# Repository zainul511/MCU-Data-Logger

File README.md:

This work was supported by material from:
Dalmaris, P. KiCad Like a Pro, 3rd Edition. Tech Explorations, 2021. ISBN 978-1-68489-093-4. 
KiCadLikeaPro3e_Course_Companion

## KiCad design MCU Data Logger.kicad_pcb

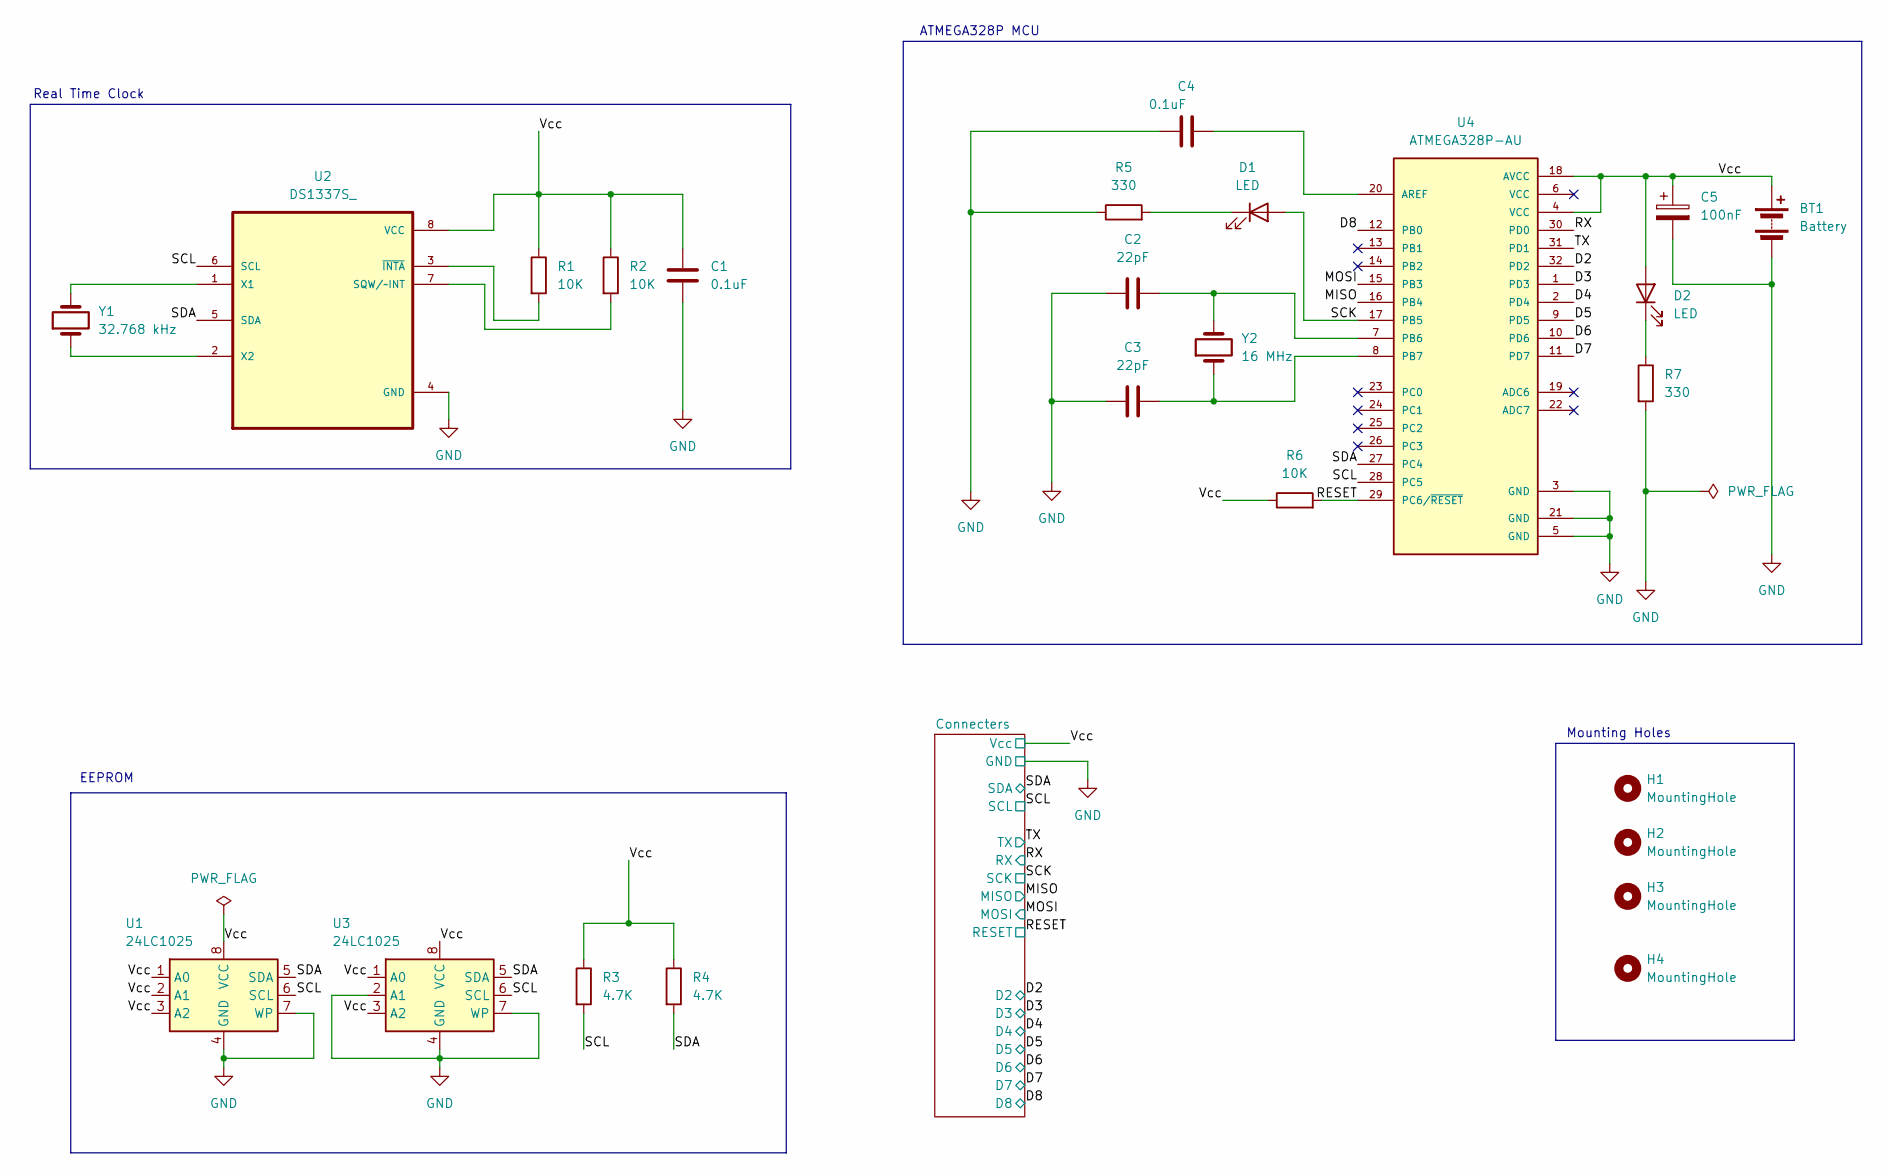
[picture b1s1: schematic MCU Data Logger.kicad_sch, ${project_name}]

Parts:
BT1: Battery; PinHeader_1x02_P2.54mm_Vertical
C1, C4: 0.1uF; C_0805_2012Metric
C2, C3: 22pF; C_0805_2012Metric
C5: 100nF; C_0805_2012Metric
D1, D2: LED; LED_0805_2012Metric
H1, H2, H3, H4: MountingHole; MountingHole_2.1mm
R1, R2, R6: 10K; R_0805_2012Metric
R3, R4: 4.7K; R_0805_2012Metric
R5, R7: 330; R_0805_2012Metric
U1, U3: 24LC1025; SOIC-8_5.3x5.3mm_P1.27mm
U2: DS1337S_; SOIC127P600X175-8N
U4: ATMEGA328P-AU; QFP80P900X900X120-32N; PARTREV 8271A
Y1: 32.768 kHz; Crystal_SMD_5032-2Pin_5.0x3.2mm_HandSoldering
Y2: 16 MHz; Crystal_SMD_5032-2Pin_5.0x3.2mm_HandSoldering

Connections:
/D2: U4.32 (PD2); also elsewhere on the board
/D3: U4.1 (PD3); also elsewhere on the board
/D4: U4.2 (PD4); also elsewhere on the board
/D5: U4.9 (PD5); also elsewhere on the board
/D6: U4.10 (PD6); also elsewhere on the board
/D7: U4.11 (PD7); also elsewhere on the board
/D8: U4.12 (PB0); also elsewhere on the board
/MISO: U4.16 (PB4); also elsewhere on the board
/MOSI: U4.15 (PB3); also elsewhere on the board
/RESET: R6.2, U4.29 (PC6/~RESET); also elsewhere on the board
/RX: U4.30 (PD0); also elsewhere on the board
/SCK: D1.2 (A), U4.17 (PB5); also elsewhere on the board
/SCL: R3.2, U1.6 (SCL), U2.6 (SCL), U3.6 (SCL), U4.28 (PC5); also elsewhere on the board
/SDA: R4.2, U1.5 (SDA), U2.5 (SDA), U3.5 (SDA), U4.27 (PC4); also elsewhere on the board
/TX: U4.31 (PD1); also elsewhere on the board
/Vcc: BT1.1 (+), C1.1, C5.1, D2.2 (A), R1.1, R2.1, R3.1, R4.1, R6.1, U1.1 (A0), U1.2 (A1), U1.3 (A2), U1.8 (VCC), U2.8 (VCC), U3.1 (A0), U3.3 (A2), U3.8 (VCC), U4.4 (VCC), U4.18 (AVCC); also elsewhere on the board
GND: BT1.2 (-), C1.2, C2.1, C3.1, C4.2, C5.2, R5.1, R7.2, U1.4 (GND), U1.7 (WP), U2.4 (GND), U3.2 (A1), U3.4 (GND), U3.7 (WP), U4.3 (GND), U4.5 (GND), U4.21 (GND); also elsewhere on the board
unnamed: D1.1 (K), R5.2
unnamed: D2.1 (K), R7.1
unnamed: R2.2, U2.7 (SQW/~INT)
unnamed: U2.1 (X1), Y1.2
unnamed: U2.2 (X2), Y1.1
unnamed: R1.2, U2.3 (~INTA)
unnamed: C4.1, U4.20 (AREF)
unnamed: C2.2, U4.7 (PB6), Y2.2
unnamed: C3.2, U4.8 (PB7), Y2.1

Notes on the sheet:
Mounting Holes
Real Time Clock
EEPROM
ATMEGA328P MCU

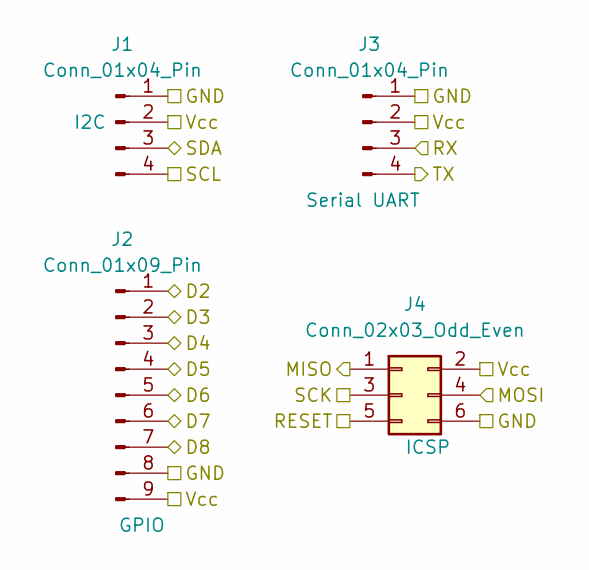
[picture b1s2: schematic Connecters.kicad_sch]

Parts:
J1, J3: Conn_01x04_Pin; PinHeader_1x04_P2.54mm_Vertical
J2: Conn_01x09_Pin; PinHeader_1x09_P2.54mm_Vertical
J4: Conn_02x03_Odd_Even; PinHeader_2x03_P2.54mm_Vertical

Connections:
/D2: J2.1; also elsewhere on the board
/D3: J2.2; also elsewhere on the board
/D4: J2.3; also elsewhere on the board
/D5: J2.4; also elsewhere on the board
/D6: J2.5; also elsewhere on the board
/D7: J2.6; also elsewhere on the board
/D8: J2.7; also elsewhere on the board
/MISO: J4.1; also elsewhere on the board
/MOSI: J4.4; also elsewhere on the board
/RESET: J4.5; also elsewhere on the board
/RX: J3.3; also elsewhere on the board
/SCK: J4.3; also elsewhere on the board
/SCL: J1.4; also elsewhere on the board
/SDA: J1.3; also elsewhere on the board
/TX: J3.4; also elsewhere on the board
/Vcc: J1.2, J2.9, J3.2, J4.2; also elsewhere on the board
GND: J1.1, J2.8, J3.1, J4.6; also elsewhere on the board

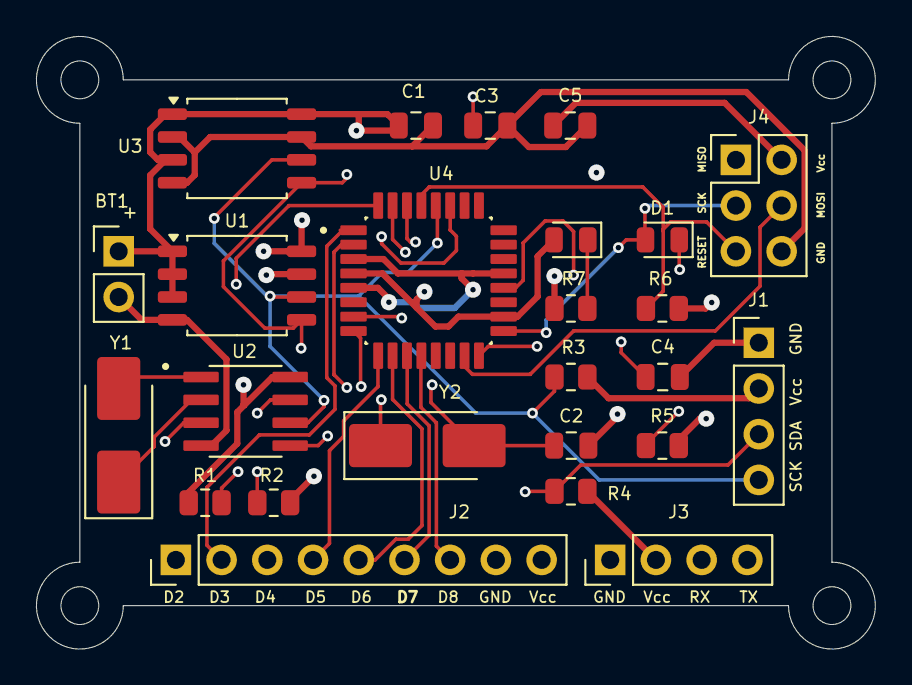
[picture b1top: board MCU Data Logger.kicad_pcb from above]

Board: 4 copper layers, 46.6 x 34.0 mm, 29 parts (0 on the bottom side), 26 nets.

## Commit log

2026-02-06 Final Version
2026-02-07 Rename folder LinkedIn to Images
2026-02-07 Add reference to KiCad Like a Pro book
